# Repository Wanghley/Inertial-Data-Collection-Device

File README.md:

<br>

>  printed circuit board and code for collecting inertial data to research purposes of movements.

## About
Hardware developed to collect inertial data from human's hands (i.e. Accelerometer, Giroscope) and temperature in order to provide an open source hardware for research related to the analysis of human movements for many purposes.<br>
This project was tested and focused on the diagnosis and prognosis of neuromotor diseases - mostly Parkinson's Disease as part of the project of scientific research [**"Visualization Strategies to Online Big Data applied in individualized medicine"**](https://github.com/Wanghley/PIBIC-Strategies-Data-Visualization-Medicine).

## Requirements
| Dependency | Platform | Description |
| :--------- | -------- | :---------- |
| [arduino_2012](https://github.com/Wanghley/Inertial-Data-Collection-Device/blob/main/lib/arduino_2012.lbr) | eagle lib | arduino schematic and layout to **Eagle** project |
| [con-headers-jp](https://github.com/Wanghley/Inertial-Data-Collection-Device/blob/main/lib/con-headers-jp.lbr) | eagle lib | schematic and layout of female pin bars to **Eagle** project |
| [DIY modules](https://github.com/Wanghley/Inertial-Data-Collection-Device/blob/main/lib/diy-modules.lbr) | eagle lib | bluetooth adaptor fotoprint and symbol to **Eagle** project |
| [KRE](https://github.com/Wanghley/Inertial-Data-Collection-Device/blob/main/lib/kre.lbr) | eagle lib | borne connector fotoprint and symbol to **Eagle** project |
| [pinhead](https://github.com/Wanghley/Inertial-Data-Collection-Device/blob/main/lib/pinhead.lbr) | eagle lib | added in the **Eagle** project for auxiliary view of pin bars |
| [TimerOne 1.1.0](https://github.com/Wanghley/Inertial-Data-Collection-Device/blob/main/lib/TimerOne-1.1.0.zip) | arduino lib | allow running a periodic interrupt function based in finer PWM control |
| [MPU6050 0.2.1](https://github.com/Wanghley/Inertial-Data-Collection-Device/blob/main/lib/MPU6050-0.2.1.zip) | arduino lib | allow MPU6050 easy control and manipulation |
| [Wire](https://www.arduino.cc/en/reference/wire) | arduino lib | allow communication over I2C protocol |
| [SoftwareSerial](https://www.arduino.cc/en/Reference/softwareSerial) | arduino lib | allow serial communication on other digital pins of the Arduino |

## Bill of Materials
| # | Designator | Qty | Description | Obs |
| - | :--------- | --- | :---------- | :---------- | 
| 1 | R1, R2 | 2 | Resistor 220R 5% (1/4W) | Used for digital protection of bluetooth module RX |
| 2 | HC-05 | 1 | HC-05 Bluetooth Module | Module of Low supply consumption for prototype communication |
| 3 | PUSH | 2 | Push Button Long Head | Push button for hardware control and operation  |
| 4 | ON/OFF | 1 | 255sb sliding switch | Sliding switch to control energy supply of the prototype |
| 5 | LED1 | 1 | COM-09590 | 2.25 V Red LED 5mm Cylindrical indicates the hardware is ready for collection |
| 6 | LED2 | 1 | COM-09590 | 2.25 V green LED 5mm Cylindrical indicates the hardware operation mode and collection in process |
| 6 | Arduino Nano | Arduino Nano | | mother board and controller |
| 7 | KRE-2P | 1 | Borne Connector | Connector to the batery |
| 8 | BATTERY CHARGER | 1 | TP4056 | Power supply adn voltage regulator to the batery |
| 9 | RGB_LED | 1 | LED RBG 5MM | RGB LED 5mm Cylindrical indicates the mode of operation of the device |

## Development
In order to run and contribute to the PCB development you must have **Eagle**  installed in your computer and then use the .sch to work on the circuit itself and the .brd to work in the layout design.

Now, for the development under de code of hardware control you must have Arduino IDE or similar to work on the .ino code plus all the libraries mentioned above on the field [Requirements](#Requirements).

## Versioning
We use [SemVer 2.0.0](https://semver.org/spec/v2.0.0.html) for versioning. For the versions available, see the [tags on this repository](https://github.com/Wanghley/Inertial-Data-Collection-Device/tags).

## Authors
<table>
  <tr>
    <td align="center">
      <a href="https://github.com/wanghley">
        <br>
        <sub>
          <b>Wanghley Soares Martins</b>
        </sub>
      </a>
      <p>Researcher</p>
    </td>
    <td align="center">
      <a href="https://github.com/oliveirafhm">
        <br>
        <sub>
          <b>Fábio Henrique M Oliveira</b>
        </sub>
      </a>
      <p>Research Advisor</p>
    </td>
  </tr>
</table>

See also the list of [contributors](https://github.com/Wanghley/PIBIC-Strategies-Data-Visualization-Medicine/contributors) who participated in this project.

## License
This project is licensed under the CC BY-NC-SA 4.0 License - see the [LICENSE.md](LICENSE.md) file for details

## Acknowledge
*   Remember, the project is free for you to use, manipulate, and change. However, I am just asking you to mention us in any copy, modification as the root of your development. We would also appreciate you citating us in any paper you publish using any knowledge we had developed here.
*   I would advice you to try out the hardware with an analysis of the result data.
*   If you want an easier software for hardware control, check out the [CONTROL SOFTWARE](https://github.com/Wanghley/PIBIC-Strategies-Data-Visualization-Medicine)

## Gallery
General view of the projected PCB. For more images go to [images/](https://github.com/Wanghley/Inertial-Data-Collection-Device/tree/main/images) and if you still want to see more you can see 3D views on [view/](https://github.com/Wanghley/Inertial-Data-Collection-Device/tree/main/view)

|  | |
|-|-|

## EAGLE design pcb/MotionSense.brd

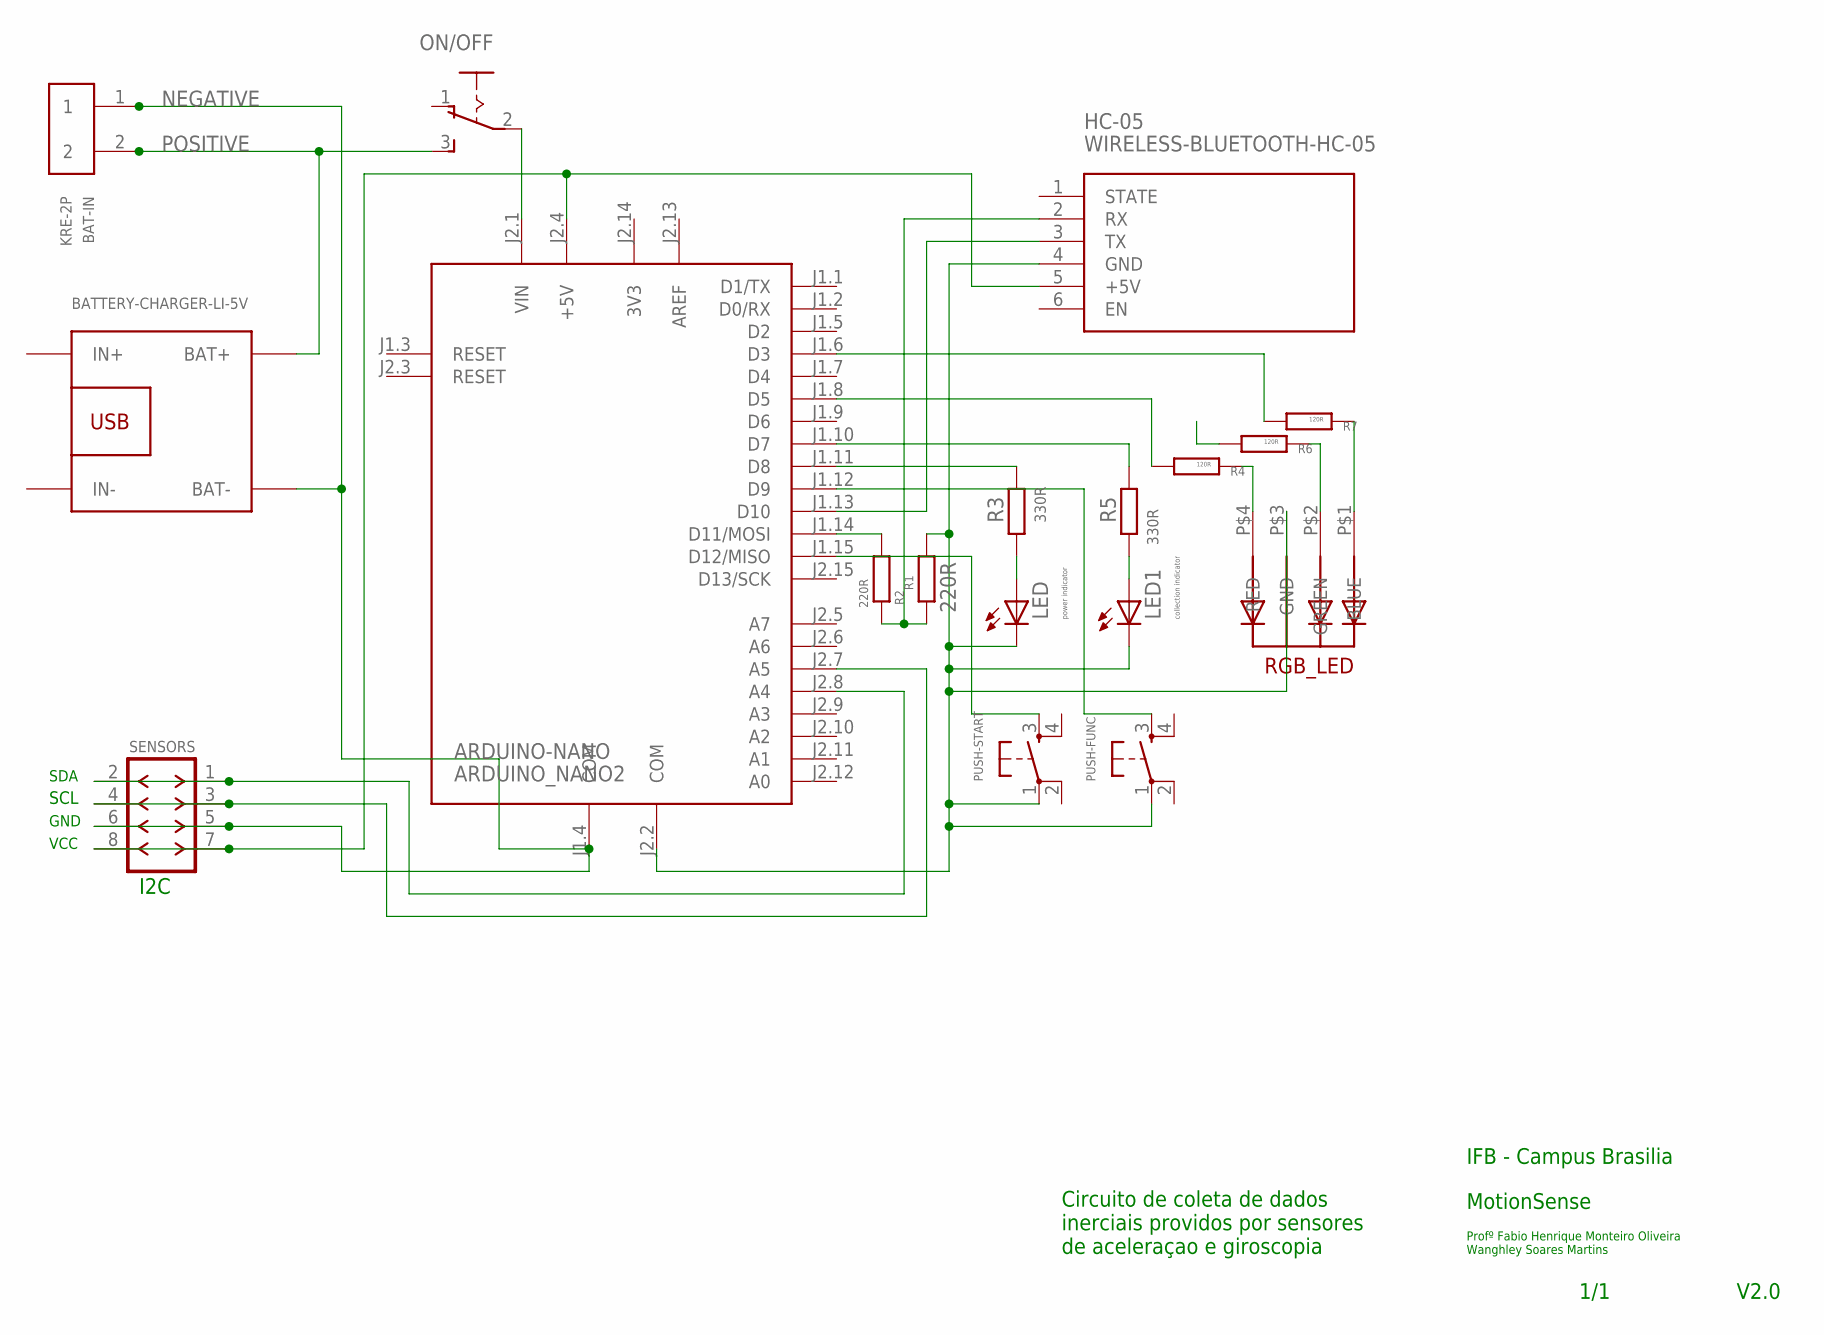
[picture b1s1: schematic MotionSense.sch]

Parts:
ARDUINO-NANO: ARDUINO_NANO2
BAT-IN: KRE-2P
HC-05: WIRELESS-BLUETOOTH-HC-05
LED: power indicator; LED5MM
LED1: collection indicator; LED5MM
ON/OFF: 255SB
PUSH-FUNC: DTS-6
PUSH-START: DTS-6
R1, R2: 220R; 0207/10
R3, R5: 330R; 0207/10
R4, R6, R7: 120R; 0204/7
RGB_LED: 5MMRGBLED; LED5MMRGB
SENSORS: F-2X04-DIL-2MM_M; DIL-2MM-2X04_M
U$1: BATTERY-CHARGER-LI-5V

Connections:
3V3: ARDUINO-NANO.J2.14 (3V3)
AREF: ARDUINO-NANO.J2.13 (AREF)
unnamed: LED.A, R3.1
unnamed: ARDUINO-NANO.J2.4 (+5V), HC-05.5 (+5V), SENSORS.7, SENSORS.8
unnamed: ARDUINO-NANO.J1.14 (D11/MOSI), R2.1
unnamed: ARDUINO-NANO.J2.2 (COM), HC-05.4 (GND), LED.K (C), LED1.K (C), PUSH-FUNC.1, PUSH-START.1, R1.2, RGB_LED.P$3 (GND)
unnamed: ARDUINO-NANO.J1.13 (D10), HC-05.3 (TX)
unnamed: HC-05.2 (RX), R1.1, R2.2
unnamed: ARDUINO-NANO.J2.7 (A5), SENSORS.3, SENSORS.4
unnamed: ARDUINO-NANO.J2.8 (A4), SENSORS.1, SENSORS.2
unnamed: ARDUINO-NANO.J1.10 (D7), R5.2
unnamed: ARDUINO-NANO.J1.15 (D12/MISO), PUSH-START.3
unnamed: ARDUINO-NANO.J2.1 (VIN), ON/OFF.2
unnamed: ARDUINO-NANO.J1.12 (D9), PUSH-FUNC.3
unnamed: ARDUINO-NANO.J1.11 (D8), R3.2
unnamed: LED1.A, R5.1
unnamed: R4.2, RGB_LED.P$4 (RED)
unnamed: R6.2, RGB_LED.P$2 (GREEN)
unnamed: R7.2, RGB_LED.P$1 (BLUE)
unnamed: ARDUINO-NANO.J1.8 (D5), R4.1
unnamed: ARDUINO-NANO.J1.6 (D3), R7.1
NEGATIVE: ARDUINO-NANO.J1.4 (COM), BAT-IN.1, SENSORS.5, SENSORS.6, U$1.BAT-
POSITIVE: BAT-IN.2, ON/OFF.3 (S), U$1.BAT+

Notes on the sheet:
Circuito de coleta de dados inerciais providos por sensores de aceleraçao e giroscopia
MotionSense
IFB - Campus Brasilia
Profº Fabio Henrique Monteiro Oliveira Wanghley Soares Martins
V2.0
1/1
I2C
VCC
GND
SCL
SDA

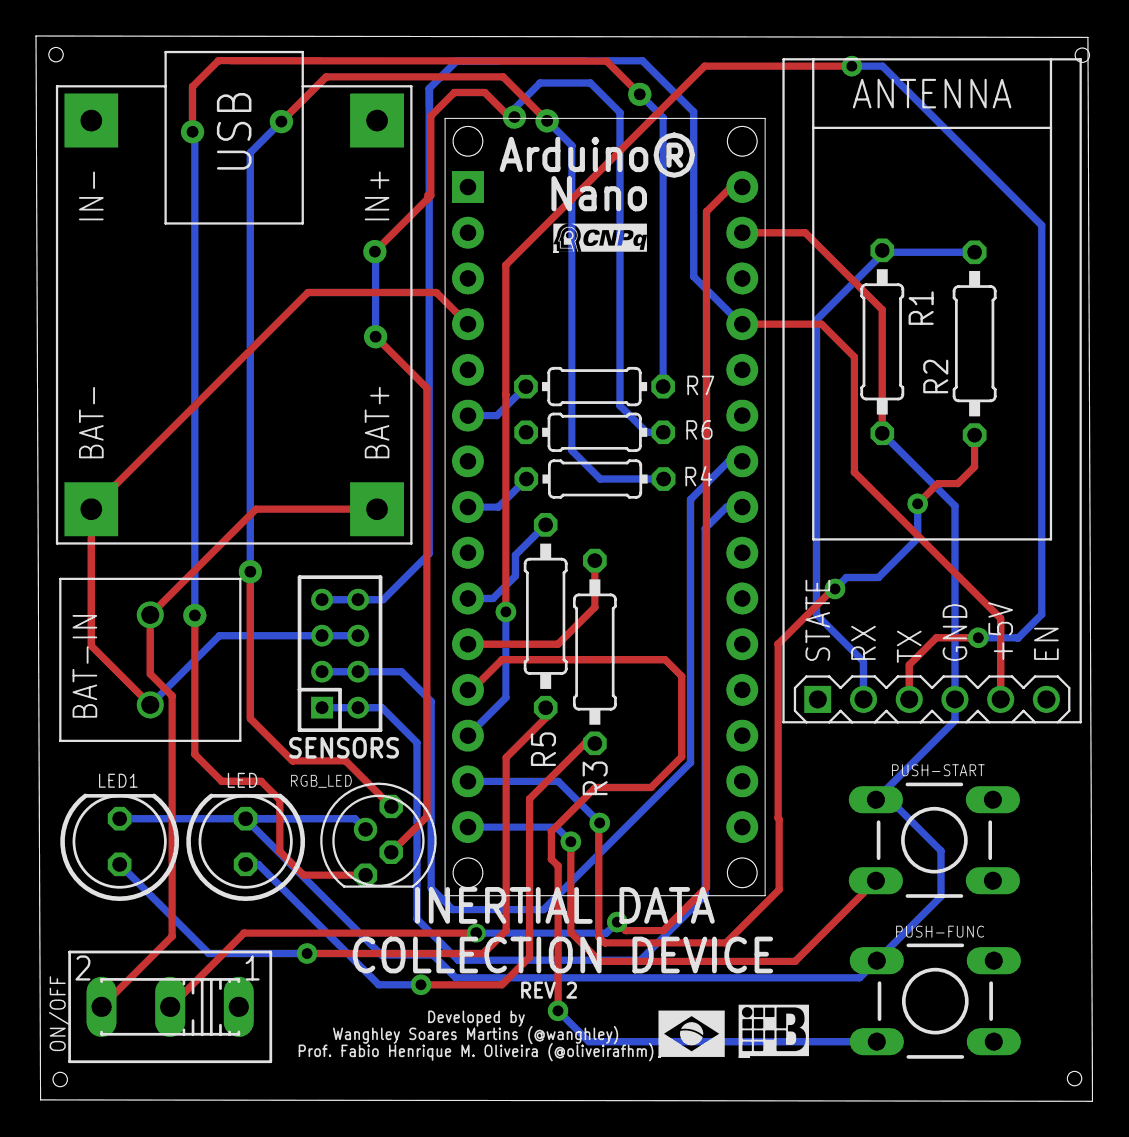
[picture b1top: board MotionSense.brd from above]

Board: 2 copper layers, 58.7 x 59.2 mm, 18 parts (0 on the bottom side), 21 nets.

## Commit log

2021-07-21 [UPDATE] Wrong ports and errors in design fixing
2021-07-21 [UPDATE] Fixing airwire, dimesion, drill distance & overlap errors in electronic design
2021-07-21 [UPDATE] Versionning information addition
2021-07-21 [UPDATE] power and collection led connection inverted correction
2021-07-21 [UPDATE] connecting new wires to LEDs after schematic error correction
2021-07-21 [UPDATE] firmware led inverted correction for compatibility between previous hardware and newer versions
2021-07-21 [UPDATE] CC BY-NC-SA 4.0 licensing
2021-07-21 [UPDATE] readme badges
2021-07-22 [UPDATE] unecessary comments removed
2021-07-23 [UPDATE] version badge
2022-02-10 [UPDATE] device parts diagram in EN added
2022-02-10 [UPDATE] Box (case) view added
2022-02-10 [UPDATE] better quality box view image
2022-02-10 [REFACTOR] using right versioning technique for assembled picture view of the prototype
2022-02-10 [REFACTOR] using right versioning technique for board view
2022-02-10 [REFACTOR] using right versioning technique for pcb and sch view
2022-02-10 [ADD] Box case 3D modeling added
2022-02-10 [ADD] Cap case 3D modeling added
2022-02-10 [ADD] Case 3D modeling added
2022-02-10 [UPDATE] correcting design and adding new information & more details about licensing
2022-02-11 [UPDATE] README version badge

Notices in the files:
parts and their libraries:
diy-modules: Released under the Creative Commons Attribution 4.0 International License: http://creativecommons.org/licenses/by/4.0
con-headers-jp: Copyright (C) 2008, Bob Starr
